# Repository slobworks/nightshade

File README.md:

This is, for all intents and purposes, a maxed-out version of the open-source, Nightshade CL-GD542x VGA card project. Basically, what this board offers the regular version is support for up to 2 megabytes of FPM DRAM installed. This board has been built by me and its basic operation verified (it works). I have _not_ tested the VESA Feature Connector, however; I am not certain that the pinout is compliant.

It's got the usual Nightshade features:

- Dedicated regulator for the internal RAMDAC, and TL431+MMBT3904 IREF circuit, for improved video quality
- Four-layer PCB and hand-tuned return paths for (hopefully) reduced noise pickup
- Supports N-well CL-GD542x chips, starting from late revision CL-GD5422 all the way up to CL-GD5429 (though you may have to change strapping resistors as needed)
- Custom footprints with longer pads for the more difficult components, to ease hand assembly using a soldering iron
- Emphasis on implementation simplicity (added regulator aside) for reduced part count and effort needed to assemble the board
- Silkscreen decorations drawn by me

The Pro variant was originally intended as a mild satire of what the 'ideal' Cirrus ISA VGA card should be, but then it spiralled out of control and became an actually viable product of its own. And it's scalable: if you don't want specific functionality (such as the second megabyte, serial EEPROM, VESA Feature Connector or the high byte BIOS socket plus its accompanying 74HCT244), then simply don't fit them.

BIOS files (apart from SEEPROM image) *not* provided here, due to uncertainty regarding the copyright. It does require a _non-interleaved_ VGA BIOS in order for it to work; most of the Cirrus BIOS files you find online are 'interleaved'. Depending on the functionality you want:
- If you want to use a BitBLT chip (GD5426 or better) and want to experiment with 2MB, you can nonetheless find a suitable (albeit padded to 64K) file, isamalaysia.bin (1.41), on the CL-GD5428 page of the VGA Legacy MkIII museum. This file has been tested and works; if your EPROM programmer complains about file size when writing 27C256, then split the file into two 32768-byte files, and use the first half to program your BIOS chips. (If you're using a 27C512, _don't_ burn this file directly to it even though it's padded; you must first split the file, and then double up the first, non-empty half. See the following paragraph.)
- If you want Serial EEPROM functionality but aren't planning on using 2MB, then you'll need a BIOS from an ISA GD542x card in order for the Serial EEPROM function to work properly. (One such BIOS that was tested to work was from a Gainward GD5424 ISA VGA card.) You will also need to pre-initialize the serial EEPROM with a valid image *before* soldering the 93C46A to the card.
- On the other hand, if all you want is just a working GD542x card, and don't care about either Serial EEPROM or 2MB, then just use whatever non-scrambled GD542x BIOS is convenient. (The beforementioned isamalaysia.bin is a reasonable candidate.)

For 27C512s, you must double up the _non-blank_ contents of the BIOS (in DOS or Windows command line, a command like 'copy /b vgabios.bin+vgabios.bin outbios.bin' is sufficient).

16-bit BIOS mode requires two PROM/EPROM/EEPROM/flash chips with identical BIOS contents.

Made in KiCAD 9.x.
Also includes gerber files so you can try it out for yourself.

Bill of materials (all parts are Surface Mount Device / SMD unless indicated otherwise):
- 1x Cirrus Logic CL-GD542x graphic chip, PQFP-160
- 2x (1MB) or 4x (2MB) 424260-compatible FPM 256Kx16 DRAM chips rated at least 70ns, SOJ-40 (this might require you to cannibalize parts from other broken cards, or roll the dice on eBay)
- 1x DIP-28 through-hole socket (2 needed for 16-bit BIOS mode)
- 1x 27C256 or compatible PROM/EPROM/flash ROM chip for BIOS, DIP-28 (2 needed for 16-bit BIOS mode)
- 1x 14.31818MHz 5032 SMD crystal (https://www.digikey.com/en/products/detail/qst/QT532G-14-31818MBBK-T/26975047)
- 1x 74HCT244, SSOP-20 or TSSOP-20 (2 needed for 16-bit BIOS mode)
- 1x LF50 or 78M05 5V LDO regulator, DPAK (https://www.digikey.com/en/products/detail/stmicroelectronics/LF50CDT-TR/591636)
- 1x TL431DBZ, SOT-23-3 (https://www.digikey.com/en/products/detail/texas-instruments/TL431BQDBZR/714694)
- 1x MMBT3904 NPN small signal transistor, SOT-23-3  (https://www.digikey.com/en/products/detail/taiwan-semiconductor-corporation/MMBT3904H-RFG/26741367)
- (Optional) 1x NM93C46 or equivalent SOIC-8 serial EEPROM (you need the one with x16 mode support) - you WILL need to initialize the serial EEPROM with a valid image *before* assembling it onto the card. Please check the directory /seeprom to get a generic image with all sub-1280x1024 SVGA refresh rates set to 60 Hz. You will also need a BIOS image from an *ISA* GD542x card for the SEEPROM functionality to work; most generic 542x BIOSes were compiled for the VLB variants, which this functionality is disabled.
- 3x 2-pin, 2.54mm pitch male jumper connectors
- (Optional) 1x 2x13 pin, 2.52mm pitch male header for VESA Feature Connector
- 1x DSUB-15-HD right angle through hole VGA connector (something akin to this: https://www.digikey.com/en/products/detail/assmann-wsw-components/A-HDF15A-KG-TAXB/1241905)
- 25x 0.1uF 0805/2012 metric ceramic caps of X5R/X7R type (https://www.digikey.com/en/products/detail/samsung-electro-mechanics/CL21B104KACNNNC/3886757)
- 7x 10uF 16V+ 2012/3216 metric ceramic caps of X5R/X7R type (these work well: https://www.digikey.com/en/products/detail/samsung-electro-mechanics/CL31B106KAHNNNE/3887462)
- 1x 22~100uF 16V 5mm x 5.3mm (or equivalent) SMD electrolytic capacitor - the higher the uF value, the better the performance, up to a point
- 4x 2.2u 0805/2012 metric ceramic caps of X5R/X7R type (1uF will likely work too)
- 1x 0.01uF / 10nF 0805/2012 metric ceramic capacitor of X5R/X7R type
- 5x 47pF 0805/2012 metric ceramic caps of C0G type
- 2x 18pF 0805/2012 metric ceramic caps of C0G type
- 1x 10K ohm 0805/2012 metric resistor
- 6x 6.8K ohm 0805/2012 metric resistors
- 5x 1K ohm 0805/2012 metric resistor
- 1x 300 ohm 0805/2012 metric resistor
- 1x 100 ohm 0805/2012 metric resistor
- 5x 75 ohm 0805/2012 metric resistors
- 1x 47 ohm 0805/2012 metric resistor
- 6x 33 ohm 0805/2012 metric resistors
- 3x 16 ohm 0805/2012 metric resistors
- (Optional) 1x PTC resettable, 9V 200mA, 0805/2012 metric polyfuse (https://www.digikey.com/en/products/detail/littelfuse-inc/0805L020YR/1212820) - this is only needed if you want to supply +5V to pin 9 of the VGA connector
- 3x 0.22~22 ohm @ 100MHz, 1210/3216 metric ferrite beads

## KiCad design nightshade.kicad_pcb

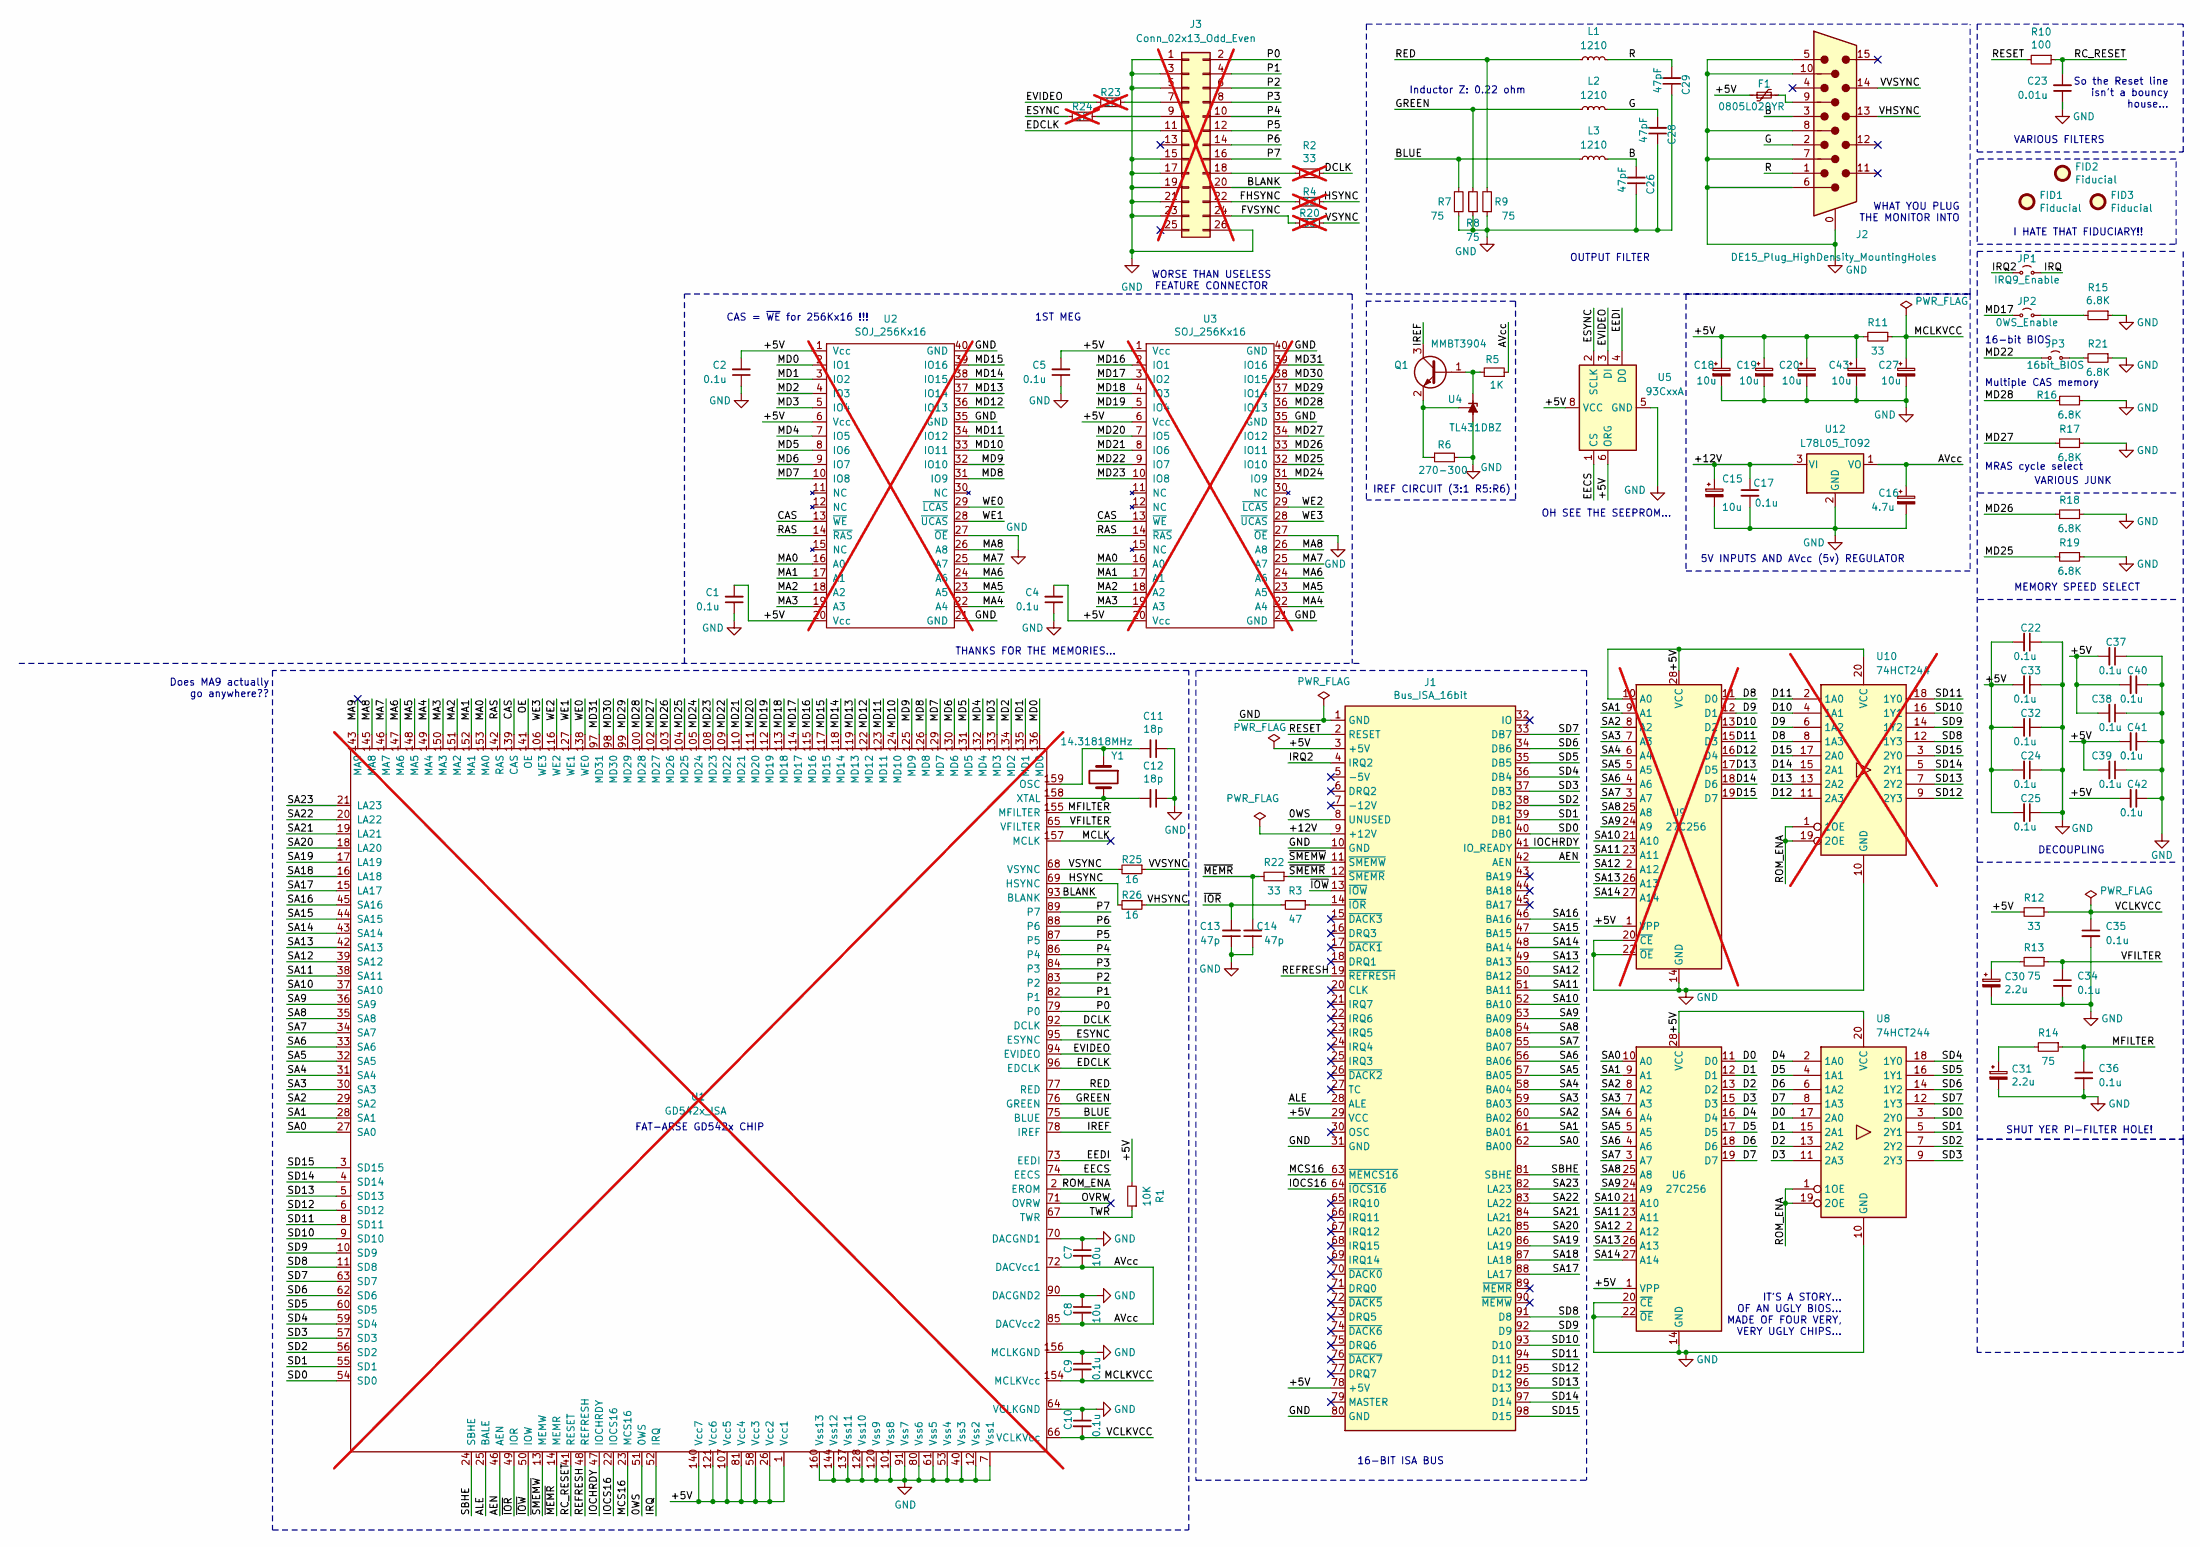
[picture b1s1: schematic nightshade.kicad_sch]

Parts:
C1, C2, C4, C5, C9, C10, C17, C22, C24, C25, C32, C33, C34, C35, C36, C37, C38, C39, C40, C41, C42: 0.1u; C_0805_2012Metric
C7, C8, C15, C18, C19, C20, C27, C43: 10u; C_1206_3216Metric
C11, C12: 18p; C_0805_2012Metric
C13, C14: 47p; C_0805_2012Metric
C16: 4.7u; CP_Elec_3x5.4
C23: 0.01u; C_0805_2012Metric
C26, C28, C29: 47pF; C_0603_1608Metric
C30, C31: 2.2u; C_0805_2012Metric
F1: 0805L020YR; Fuse_0805_2012Metric
FID1, FID2, FID3: Fiducial; Fiducial_1mm_Mask2mm
J1: Bus_ISA_16bit; BUS_AT
J2: DE15_Plug_HighDensity_MountingHoles; DSUB-15-HD
J3: Conn_02x13_Odd_Even; PinHeader_2x13_P2.54mm_Vertical; not fitted
JP1: IRQ9_Enable; PinHeader_1x02_P2.54mm_Vertical
JP2: 0WS_Enable; PinHeader_1x02_P2.54mm_Vertical
JP3: 16bit_BIOS; PinHeader_1x02_P2.54mm_Vertical
L1, L2, L3: 1210; L_1206_3216Metric
Q1: MMBT3904; SOT-23
R1: 10K; R_0805_2012Metric
R2, R4, R20: 33; R_0603_1608Metric; not fitted
R3: 47; R_0805_2012Metric
R5: 1K; R_0805_2012Metric
R6: 270-300; R_0805_2012Metric
R7, R8, R9: 75; R_0603_1608Metric
R10: 100; R_0805_2012Metric
R11, R12: 33; R_0603_1608Metric
R13, R14: 75; R_0805_2012Metric
R15, R16, R17, R18, R19, R21: 6.8K; R_0805_2012Metric
R22: 33; R_0805_2012Metric
R23, R24: 1K; R_0603_1608Metric; not fitted
R25, R26: 16; R_0603_1608Metric
U1: GD542x_ISA; PQFP-160_28x28mm_P0.65mm; not fitted
U2, U3: SOJ_256Kx16; SOJ-40_10.16x26.44mm_P1.27mm; not fitted
U4: TL431DBZ; SOT-23
U5: 93CxxA; SOIC-8_DMP-8
U6: 27C256; DIP-28_W15.24mm_Socket
U8: 74HCT244; SSOP-20_4.4_5.3x6.5mm_P0.65mm
U9: 27C256; DIP-28_W15.24mm_Socket; not fitted
U10: 74HCT244; SSOP-20_4.4_5.3x6.5mm_P0.65mm; not fitted
U12: L78L05_TO92; TO-92_Inline
Y1: 14.31818MHz; Crystal_SMD_5032-2Pin_5.0x3.2mm_HandSoldering

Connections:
/0WS: J1.8 (UNUSED), U1.51 (0WS)
/+5V: C1.2, C2.2, C4.2, C5.2, C18.1, C19.1, C20.1, C22.2, C24.2, C25.2, C32.2, C33.2, C37.2, C38.2, C39.2, C40.2, C41.2, C42.2, C43.1, F1.1, J1.3 (+5V), J1.29 (VCC), J1.78 (+5V), R1.2, R11.2, R12.2, U1.1 (Vcc1), U1.26 (Vcc2), U1.58 (Vcc3), U1.81 (Vcc4), U1.107 (Vcc5), U1.121 (Vcc6), U1.140 (Vcc7), U2.1 (Vcc), U2.6 (Vcc), U2.20 (Vcc), U3.1 (Vcc), U3.6 (Vcc), U3.20 (Vcc), U5.6 (ORG), U5.8 (VCC), U6.1 (VPP), U6.28 (VCC), U8.20 (VCC), U9.1 (VPP), U9.10 (A0), U9.28 (VCC), U10.20 (VCC)
/+12V: C15.1, C17.1, J1.9 (+12V), U12.3 (VI)
/AEN: J1.42 (AEN), U1.46 (AEN)
/ALE: J1.28 (ALE), U1.25 (BALE)
/AVcc: C7.2, C8.2, C16.1, R5.1, U1.72 (DACVcc1), U1.85 (DACVcc2), U12.1 (VO)
/B: C26.2, J2.3, L3.2
/BLANK: J3.20, U1.93 (BLANK)
/BLUE: L3.1, R7.2, U1.75 (BLUE)
/CAS: U1.139 (CAS), U2.13 (~WE), U3.13 (~WE)
/D0: U6.11 (D0), U8.17 (2A0)
/D1: U6.12 (D1), U8.15 (2A1)
/D2: U6.13 (D2), U8.13 (2A2)
/D3: U6.15 (D3), U8.11 (2A3)
/D4: U6.16 (D4), U8.2 (1A0)
/D5: U6.17 (D5), U8.4 (1A1)
/D6: U6.18 (D6), U8.6 (1A2)
/D7: U6.19 (D7), U8.8 (1A3)
/D8: U9.11 (D0), U10.8 (1A3)
/D9: U9.12 (D1), U10.6 (1A2)
/D10: U9.13 (D2), U10.4 (1A1)
/D11: U9.15 (D3), U10.2 (1A0)
/D12: U9.16 (D4), U10.11 (2A3)
/D13: U9.17 (D5), U10.13 (2A2)
/D14: U9.18 (D6), U10.15 (2A1)
/D15: U9.19 (D7), U10.17 (2A0)
/DCLK: R2.1, U1.92 (DCLK)
/EDCLK: J3.11, U1.96 (EDCLK)
/EECS: U1.74 (EECS), U5.1 (CS)
/EEDI: U1.73 (EEDI), U5.4 (DO)
/ESYNC: R24.2, U1.95 (ESYNC), U5.2 (SCLK)
/EVIDEO: R23.2, U1.94 (EVIDEO), U5.3 (DI)
/FHSYNC: J3.22, R4.2
/FVSYNC: J3.24, R20.2
/G: C28.2, J2.2, L2.2
/GREEN: L2.1, R8.2, U1.76 (GREEN)
/HSYNC: R4.1, R26.2, U1.69 (HSYNC)
/IOCHRDY: J1.41 (IO_READY), U1.47 (IOCHRDY)
/IOCS16: J1.64 (~IOCS16), U1.22 (IOCS16)
/IREF: Q1.3 (C), U1.78 (IREF)
/IRQ: JP1.2 (B), U1.52 (IRQ)
/IRQ2: J1.4 (IRQ2), JP1.1 (A)
/MA0: U1.153 (MA0), U2.16 (A0), U3.16 (A0)
/MA1: U1.152 (MA1), U2.17 (A1), U3.17 (A1)
/MA2: U1.151 (MA2), U2.18 (A2), U3.18 (A2)
/MA3: U1.150 (MA3), U2.19 (A3), U3.19 (A3)
/MA4: U1.149 (MA4), U2.22 (A4), U3.22 (A4)
/MA5: U1.148 (MA5), U2.23 (A5), U3.23 (A5)
/MA6: U1.147 (MA6), U2.24 (A6), U3.24 (A6)
/MA7: U1.146 (MA7), U2.25 (A7), U3.25 (A7)
/MA8: U1.145 (MA8), U2.26 (A8), U3.26 (A8)
/MA9: U1.143 (MA9)
/MCLK: U1.157 (MCLK)
/MCLKVCC: C9.2, C27.1, R11.1, U1.154 (MCLKVcc)
/MCS16: J1.63 (~MEMCS16), U1.23 (MCS16)
/MD0: U1.136 (MD0), U2.2 (IO1)
/MD1: U1.135 (MD1), U2.3 (IO2)
/MD2: U1.134 (MD2), U2.4 (IO3)
/MD3: U1.133 (MD3), U2.5 (IO4)
/MD4: U1.132 (MD4), U2.7 (IO5)
/MD5: U1.131 (MD5), U2.8 (IO6)
/MD6: U1.130 (MD6), U2.9 (IO7)
/MD7: U1.129 (MD7), U2.10 (IO8)
/MD8: U1.126 (MD8), U2.31 (IO9)
/MD9: U1.125 (MD9), U2.32 (IO10)
/MD10: U1.124 (MD10), U2.33 (IO11)
/MD11: U1.123 (MD11), U2.34 (IO12)
/MD12: U1.122 (MD12), U2.36 (IO13)
/MD13: U1.119 (MD13), U2.37 (IO14)
/MD14: U1.118 (MD14), U2.38 (IO15)
/MD15: U1.117 (MD15), U2.39 (IO16)
/MD16: U1.115 (MD16), U3.2 (IO1)
/MD17: JP2.1 (A), U1.114 (MD17), U3.3 (IO2)
/MD18: U1.113 (MD18), U3.4 (IO3)
/MD19: U1.112 (MD19), U3.5 (IO4)
/MD20: U1.111 (MD20), U3.7 (IO5)
/MD21: U1.110 (MD21), U3.8 (IO6)
/MD22: JP3.1 (A), U1.109 (MD22), U3.9 (IO7)
/MD23: U1.108 (MD23), U3.10 (IO8)
/MD24: U1.105 (MD24), U3.31 (IO9)
/MD25: R19.2, U1.104 (MD25), U3.32 (IO10)
/MD26: R18.2, U1.103 (MD26), U3.33 (IO11)
/MD27: R17.2, U1.102 (MD27), U3.34 (IO12)
/MD28: R16.2, U1.100 (MD28), U3.36 (IO13)
/MD29: U1.99 (MD29), U3.37 (IO14)
/MD30: U1.98 (MD30), U3.38 (IO15)
/MD31: U1.97 (MD31), U3.39 (IO16)
/MFILTER: C36.1, R14.1, U1.155 (MFILTER)
/OE: U1.141 (OE)
/OVRW: U1.71 (OVRW)
/P0: J3.2, U1.79 (P0)
/P1: J3.4, U1.82 (P1)
/P2: J3.6, U1.83 (P2)
/P3: J3.8, U1.84 (P3)
/P4: J3.10, U1.86 (P4)
/P5: J3.12, U1.87 (P5)
/P6: J3.14, U1.88 (P6)
/P7: J3.16, U1.89 (P7)
/R: C29.2, J2.1, L1.2
/RAS: U1.142 (RAS), U2.14 (~RAS), U3.14 (~RAS)
/RC_RESET: C23.2, R10.1, U1.41 (RESET)
/RED: L1.1, R9.2, U1.77 (RED)
/REFRESH: J1.19 (~REFRESH), U1.48 (REFRESH)
/RESET: J1.2 (RESET), R10.2
/ROM_ENA: U1.2 (EROM), U8.1 (1OE), U8.19 (2OE), U10.1 (1OE), U10.19 (2OE)
/SA0: J1.62 (BA00), U1.27 (SA0), U6.10 (A0)
/SA1: J1.61 (BA01), U1.28 (SA1), U6.9 (A1), U9.9 (A1)
/SA2: J1.60 (BA02), U1.29 (SA2), U6.8 (A2), U9.8 (A2)
/SA3: J1.59 (BA03), U1.30 (SA3), U6.7 (A3), U9.7 (A3)
/SA4: J1.58 (BA04), U1.31 (SA4), U6.6 (A4), U9.6 (A4)
/SA5: J1.57 (BA05), U1.32 (SA5), U6.5 (A5), U9.5 (A5)
/SA6: J1.56 (BA06), U1.33 (SA6), U6.4 (A6), U9.4 (A6)
/SA7: J1.55 (BA07), U1.34 (SA7), U6.3 (A7), U9.3 (A7)
/SA8: J1.54 (BA08), U1.35 (SA8), U6.25 (A8), U9.25 (A8)
/SA9: J1.53 (BA09), U1.36 (SA9), U6.24 (A9), U9.24 (A9)
/SA10: J1.52 (BA10), U1.37 (SA10), U6.21 (A10), U9.21 (A10)
/SA11: J1.51 (BA11), U1.38 (SA11), U6.23 (A11), U9.23 (A11)
/SA12: J1.50 (BA12), U1.39 (SA12), U6.2 (A12), U9.2 (A12)
/SA13: J1.49 (BA13), U1.42 (SA13), U6.26 (A13), U9.26 (A13)
/SA14: J1.48 (BA14), U1.43 (SA14), U6.27 (A14), U9.27 (A14)
/SA15: J1.47 (BA15), U1.44 (SA15)
/SA16: J1.46 (BA16), U1.45 (SA16)
/SA17: J1.88 (LA17), U1.15 (LA17)
/SA18: J1.87 (LA18), U1.16 (LA18)
/SA19: J1.86 (LA19), U1.17 (LA19)
/SA20: J1.85 (LA20), U1.18 (LA20)
/SA21: J1.84 (LA21), U1.19 (LA21)
/SA22: J1.83 (LA22), U1.20 (LA22)
/SA23: J1.82 (LA23), U1.21 (LA23)
/SBHE: J1.81 (SBHE), U1.24 (SBHE)
/SD0: J1.40 (DB0), U1.54 (SD0), U8.3 (2Y0)
/SD1: J1.39 (DB1), U1.55 (SD1), U8.5 (2Y1)
/SD2: J1.38 (DB2), U1.56 (SD2), U8.7 (2Y2)
/SD3: J1.37 (DB3), U1.57 (SD3), U8.9 (2Y3)
/SD4: J1.36 (DB4), U1.59 (SD4), U8.18 (1Y0)
/SD5: J1.35 (DB5), U1.60 (SD5), U8.16 (1Y1)
/SD6: J1.34 (DB6), U1.62 (SD6), U8.14 (1Y2)
/SD7: J1.33 (DB7), U1.63 (SD7), U8.12 (1Y3)
/SD8: J1.91 (D8), U1.11 (SD8), U10.12 (1Y3)
/SD9: J1.92 (D9), U1.10 (SD9), U10.14 (1Y2)
/SD10: J1.93 (D10), U1.9 (SD10), U10.16 (1Y1)
/SD11: J1.94 (D11), U1.8 (SD11), U10.18 (1Y0)
/SD12: J1.95 (D12), U1.6 (SD12), U10.9 (2Y3)
/SD13: J1.96 (D13), U1.5 (SD13), U10.7 (2Y2)
/SD14: J1.97 (D14), U1.4 (SD14), U10.5 (2Y1)
/SD15: J1.98 (D15), U1.3 (SD15), U10.3 (2Y0)
/TWR: R1.1, U1.67 (TWR)
/VCLKVCC: C10.2, C35.1, R12.1, U1.66 (VCLKVcc)
/VFILTER: C34.1, R13.1, U1.65 (VFILTER)
/VHSYNC: J2.13, R26.1
/VSYNC: R20.1, R25.2, U1.68 (VSYNC)
/VVSYNC: J2.14, R25.1
/WE0: U1.138 (WE0), U2.29 (~LCAS)
/WE1: U1.127 (WE1), U2.28 (~UCAS)
/WE2: U1.116 (WE2), U3.29 (~LCAS)
/WE3: U1.106 (WE3), U3.28 (~UCAS)
/~IOR: C13.2, R3.2, U1.49 (IOR)
/~IOW: J1.13 (~IOW), U1.50 (IOW)
/~MEMR: C14.2, R22.2, U1.14 (MEMR)
/~SMEMR: J1.12 (~SMEMR), R22.1
/~SMEMW: J1.11 (~SMEMW), U1.13 (MEMW)
GND: C1.1, C2.1, C4.1, C5.1, C7.1, C8.1, C9.1, C10.1, C11.1, C12.1, C13.1, C14.1, C15.2, C16.2, C17.2, C18.2, C19.2, C20.2, C22.1, C23.1, C24.1, C25.1, C26.1, C27.2, C28.1, C29.1, C30.2, C31.2, C32.1, C33.1, C34.2, C35.2, C36.2, C37.1, C38.1, C39.1, C40.1, C41.1, C42.1, C43.2, J1.1 (GND), J1.10 (GND), J1.31 (GND), J1.80 (GND), J2.0, J2.5, J2.6, J2.7, J2.8, J2.10, J3.1, J3.3, J3.5, J3.15, J3.17, J3.19, J3.21, J3.23, J3.26, R6.2, R7.1, R8.1, R9.1, R15.1, R16.1, R17.1, R18.1, R19.1, R21.1, U1.7 (Vss1), U1.12 (Vss2), U1.40 (Vss3), U1.53 (Vss4), U1.61 (Vss5), U1.64 (VCLKGND), U1.70 (DACGND1), U1.80 (Vss6), U1.90 (DACGND2), U1.91 (Vss7), U1.101 (Vss8), U1.120 (Vss9), U1.128 (Vss10), U1.137 (Vss11), U1.144 (Vss12), U1.156 (MCLKGND), U1.160 (Vss13), U2.21 (GND), U2.27 (~OE), U2.35 (GND), U2.40 (GND), U3.21 (GND), U3.27 (~OE), U3.35 (GND), U3.40 (GND), U4.3 (A), U5.5 (GND), U6.14 (GND), U6.20 (~CE), U6.22 (~OE), U8.10 (GND), U9.14 (GND), U9.20 (~CE), U9.22 (~OE), U10.10 (GND), U12.2 (GND)
unnamed: C30.1, R13.2
unnamed: C31.1, R14.2
unnamed: F1.2, J2.9
unnamed: J1.14 (~IOR), R3.1
unnamed: J3.7, R23.1
unnamed: J3.9, R24.1
unnamed: J3.18, R2.2
unnamed: JP2.2 (B), R15.2
unnamed: JP3.2 (B), R21.2
unnamed: Q1.1 (B), R5.2, U4.1 (K)
unnamed: Q1.2 (E), R6.1, U4.2 (REF)
unnamed: C11.2, U1.159 (OSC), Y1.1
unnamed: C12.2, U1.158 (XTAL), Y1.2

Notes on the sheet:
FAT-ARSE GD542x CHIP
16-BIT ISA BUS
WHAT YOU PLUG THE MONITOR INTO
DECOUPLING
So the Reset line isn't a bouncy house...
MRAS cycle select
THANKS FOR THE MEMORIES...
1ST MEG
Does MA9 actually go anywhere??
IREF CIRCUIT (3:1 R5:R6)
Inductor Z: 0.22 ohm
SHUT YER PI-FILTER HOLE!
16-bit BIOS
OH SEE THE SEEPROM...
VARIOUS FILTERS
MEMORY SPEED SELECT
I HATE THAT FIDUCIARY!!
Multiple CAS memory
VARIOUS JUNK
IT'S A STORY... OF AN UGLY BIOS... MADE OF FOUR VERY, VERY UGLY CHIPS...
OUTPUT FILTER
5V INPUTS AND AVcc (5v) REGULATOR
CAS = ~{WE} for 256Kx16 !!!
WORSE THAN USELESS FEATURE CONNECTOR

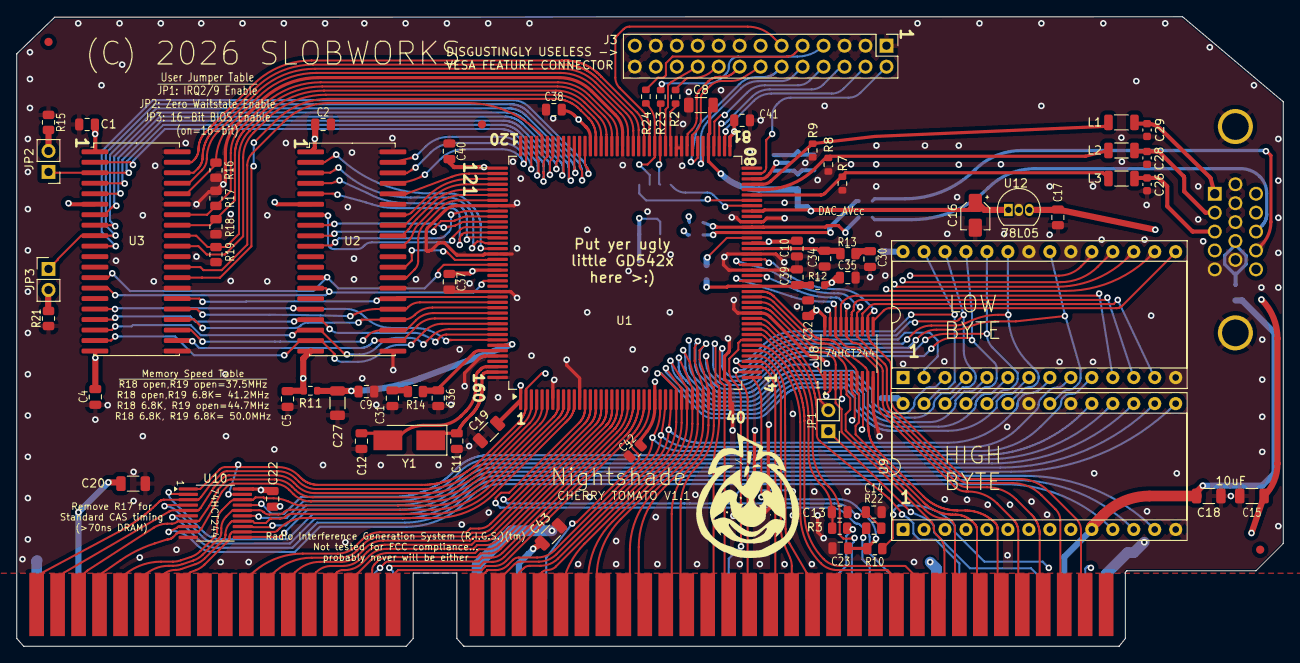
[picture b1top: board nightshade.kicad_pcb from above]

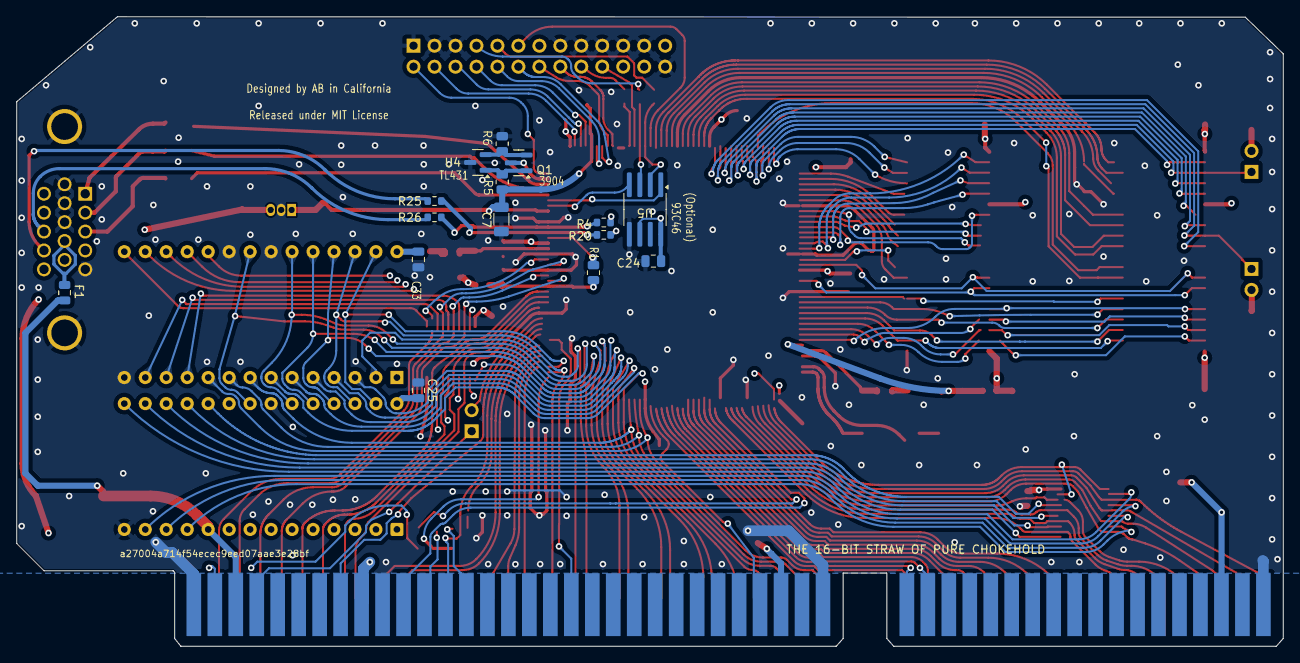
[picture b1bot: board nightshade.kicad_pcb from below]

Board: 4 copper layers, 153.4 x 76.2 mm, 91 parts (15 on the bottom side), 171 nets.

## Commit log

2025-04-14 Add files via upload
    Updated with corrected parts lists etc.
2025-04-14 Update README.md
    Pictures!
2025-06-03 Add files via upload
    Updated to KiCAD 9.x, fixed some bugs in the silkscreening
2025-06-03 Delete ~nightshade.kicad_sch.lck
    Oops
2026-01-19 Add files via upload
    Say hello to Killer Tomato!
2026-01-19 Update README.md
    Added pix!
2026-01-19 Update README.md
    formatting twiddles
2026-01-19 Update README.md
    Updated parts list (may not be complete)
2026-01-19 Add files via upload
    Added .bom file
2026-01-19 Update README.md
    Correcting component counts
2026-01-19 Update README.md
    Disambiguated 'DIP-28 socket' -> 'DIP-28 through-hole socket'.
2026-01-19 Update README.md
    Don't need the LM334 anymore :)
2026-01-19 Update README.md
    Oops, forgot about crystal
2026-01-21 Add files via upload
    A big bunch of little bug fixes, and combined a capacitor and DIP-28 socket to fix an issue where a ceramic cap was placed too close to the edge connector (mechanical stress issue).
2026-01-21 Add files via upload
    Changed combined footprint back to discrete individual cap and socket. Moved capacitor out from underneath the socket footprint. There, automated assembly should be able to install everything now.
2026-01-21 Update README.md
    Added mention about the SEEPROM
2026-01-21 Add files via upload
    Added SEEPROM image
2026-01-21 Update README.md
    typo
2026-01-22 Add files via upload
    More minor fixes.
2026-01-23 Update README.md
    Just remembered that I didn't test the VESA Feature Connector
2026-01-24 Update README.md
    Fixed stupid typos
2026-01-26 Update README.md
    attempting to fix pictures
2026-01-26 Add files via upload
    1.0a - Moderate clean-up of routing in some areas, improving ground pour contiguity and redistributing some of the ground pour vias so they're a little smarter placed in general.
2026-01-26 Update README.md
    Work with the pictures, damn you!
2026-03-06 Update README.md
    Changed 0.22uF caps to 0.1uF - I tested 0.1uF on a board and it seems to work pretty much identically to the 0.22uF fitted boards, but with cheaper parts
2026-03-06 Add files via upload
    Cheaper parts that do not affect function! Yay!
2026-03-20 Update README.md
    Provisionally renamed to 'Nightshade Pro' to avoid legal issues
2026-03-20 Update README.md
    Changed pictures
2026-03-20 Add files via upload
    Replaced all textual references to 'Killer Tomato' to less copyright infringing alternatives. Graphics are not changed yet, they will be eventually once time permits.
2026-04-11 Update README.md
    Changed link for MMBT3904 to point to non-marketplace product
2026-05-06 Update README.md
    Updated for new version
2026-05-06 Add files via upload
    Updated to Cherry Tomato V1.0 revision
2026-05-06 Update README.md
    Added bit about dnp GD542x
2026-06-17 Update README.md
    Corrected missing 1K resistors in BOM

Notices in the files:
nightshade.kicad_pcb:
(C) 2026 SLOBWORKS
Released under MIT License
